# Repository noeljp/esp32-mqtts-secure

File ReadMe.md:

# 🛰️ Projet ESP32 MQTTs – Supervision de Machines Industrielles

Ce projet permet à un **ESP32** de se connecter à un **broker MQTT sécurisé (MQTTs)** afin de publier régulièrement des mesures issues d’une machine industrielle (armoire, four, frigo, etc.). Il inclut également la réception de commandes via MQTT.

---

## 🔧 Fonctionnalités principales

- Connexion sécurisée au Wi-Fi et au broker MQTT via TLS.
- Publication périodique de données au format JSON (via `ArduinoJson`).
- Abonnement à un topic pour recevoir des commandes.
- Adaptation dynamique selon le type de machine (armoire, four, frigo...).
- Intégration de capteurs analogiques (via `ADS1115`) et d'entrées numériques.
- Configuration centralisée dans `device_config.h` et `secrets.h`.

---

## 📁 Structure du projet

```bash
.
├── src/
│   ├── main.cpp            # Fichier principal Arduino (PlatformIO ou IDE Arduino)
│   ├── device_config.h     # Paramètres matériels de la machine (type, capteurs, I/O)
│   └── secrets.h           # Identifiants WiFi et certificats TLS (à créer manuellement)
├── include/
│   └── ...
├── certs/
│   ├── ca.crt              # Certificat racine du broker MQTT
│   └── ...
├── README.md               # Ce fichier
└── platformio.ini          # Configuration PlatformIO (si utilisé)
```

---

## 🔒 Fichier `secrets.h` (à créer)

Ce fichier contient les informations sensibles de connexion :

```cpp
#pragma once

const char* ssid = "VOTRE_SSID_WIFI";
const char* password = "VOTRE_MOT_DE_PASSE_WIFI";

const char* mqtt_server = "192.168.1.100";  // Adresse IP ou nom DNS du broker
const int mqtt_port = 8883;                // Port TLS

const char* mqtt_user = "utilisateur";
const char* mqtt_pass = "motdepasse";

// Certificat du broker (fichier .crt converti en chaîne C)
const char* ca_cert = R"EOF(
-----BEGIN CERTIFICATE-----
MIID...
...contenu du certificat...
-----END CERTIFICATE-----
)EOF";
```

---

## 🚀 Démarrage rapide

### 1. Pré-requis

- Carte **ESP32**
- Broker **Mosquitto** avec TLS et mot de passe (voir [guide d’installation ici](https://mosquitto.org/man/mosquitto.conf-5.html))
- Bibliothèques Arduino :
  - `PubSubClient`
  - `ArduinoJson`
  - `Adafruit_ADS1X15`
  - `WiFiClientSecure`

### 2. Compilation

Avec PlatformIO :
```bash
pio run
pio upload
```

Avec Arduino IDE :
- Sélectionner la carte "ESP32 Dev Module"
- Ajouter manuellement les bibliothèques
- Uploader le code

---

## 🔁 Boucle principale

- Toutes les `10 secondes` :
  - Lecture des capteurs (PT100, humidité, tension, etc.)
  - Construction d’un **JSON structuré**
  - Envoi sur le topic : `test/topic`

Exemple de JSON publié :
```json
{
  "device_id": "ARM1",
  "type": "armoire",
  "status": "OK",
  "firmware": "1.0.0",
  "uptime": "12345",
  "pt100_1": {
    "value": 23.5,
    "unit": "°C",
    "type": "temperature"
  },
  ...
}
```

---

## 📥 Commandes via MQTT

Le code s'abonne automatiquement au topic `test/cmd`. Les commandes reçues peuvent être affichées ou traitées selon le besoin (fonction `callback()` à enrichir).

---

## 🛠️ Configuration machine

Le fichier `device_config.h` permet d’adapter le programme à différents types de machines :

```cpp
const char* machine_type = "armoire"; // "four", "frigo", etc.
```

Chaque type dispose de :
- Ses capteurs spécifiques
- Sa logique d'initialisation (`initMachine`)
- Ses données personnalisées dans `fillMachineData`

---

## ✅ Extensions possibles

- Support de la reconnection automatique au WiFi
- Gestion de l’OTA (mise à jour firmware via réseau)
- Affichage sur écran OLED/TFT
- Ajout de watchdog

---

## 📬 Exemple de configuration côté Mosquitto

```conf
listener 8883
cafile /etc/mosquitto/certs/ca.crt
require_certificate false
allow_anonymous false
password_file /etc/mosquitto/passwd
```

---

## 📖 Auteurs et licence

Projet développé dans le cadre d’une supervision industrielle personnalisable par [Votre Nom / Équipe].

Licence : MIT (ou autre selon votre choix)

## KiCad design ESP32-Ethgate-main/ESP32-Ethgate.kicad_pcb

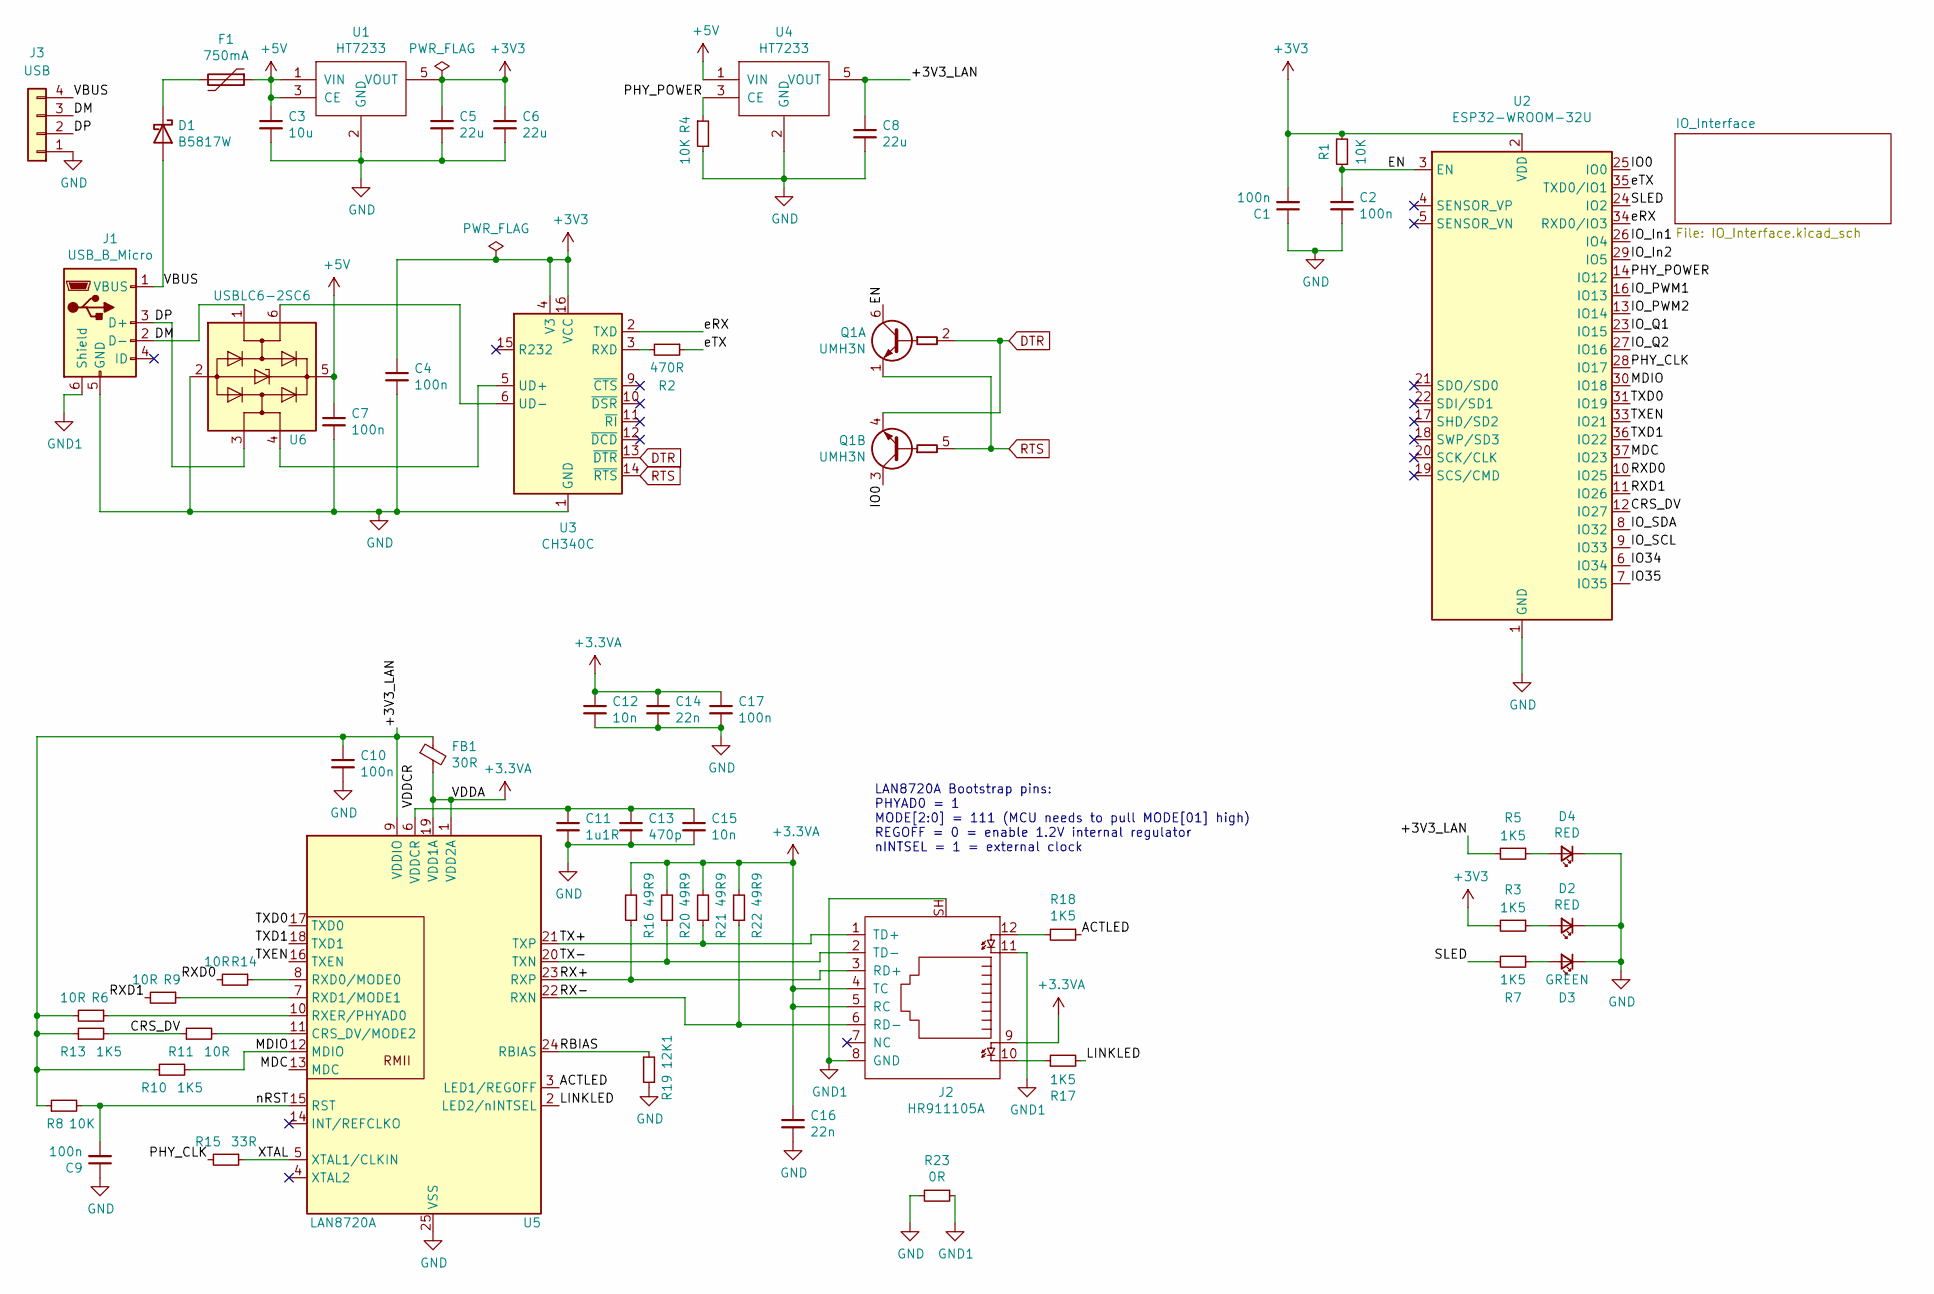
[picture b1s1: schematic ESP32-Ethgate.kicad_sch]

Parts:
C1, C2, C4, C7, C9, C10, C17: 100n; C_0603_1608Metric
C3: 10u; C_0805_2012Metric
C5, C6, C8: 22u; C_0805_2012Metric
C11: 1u1R; C_0603_1608Metric
C12, C15: 10n; C_0603_1608Metric
C13: 470p; C_0603_1608Metric
C14, C16: 22n; C_0603_1608Metric
D1: B5817W; D_SOD-323_HandSoldering
D2, D4: RED; LED_0603_1608Metric_Castellated
D3: GREEN; LED_0603_1608Metric_Castellated
F1: 750mA; Fuse_0805_2012Metric_Pad1.15x1.40mm_HandSolder
FB1: 30R; L_0603_1608Metric
J1: USB_B_Micro; USB_Micro-B_CNC_C10418
J2: HR911105A; RJ45_Hanrun_HR911105A_Oval
J3: USB; Molex_PicoBlade_53047-0410_1x04_P1.25mm_Vertical
Q1: UMH3N; SOT-363_SC-70-6_Handsoldering
R1, R4, R8: 10K; R_0603_1608Metric
R2: 470R; R_0603_1608Metric
R3, R5, R7, R10, R13, R17, R18: 1K5; R_0603_1608Metric
R6, R9, R11, R14: 10R; R_0603_1608Metric
R15: 33R; R_0603_1608Metric
R16, R20, R21, R22: 49R9; R_0603_1608Metric
R19: 12K1; R_0603_1608Metric
R23: 0R; R_0603_1608Metric
U1, U4: HT7233; SOT-23-5
U2: ESP32-WROOM-32U; ESP32-WROOM-32U-HandSoldering
U3: CH340C; SOIC-16_3.9x9.9mm_P1.27mm
U5: LAN8720A; QFN-24-1EP_4x4mm_P0.5mm_EP2.6x2.6mm
U6: USBLC6-2SC6; SOT-23-6_Handsoldering

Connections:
+3.3VA: C12.1, C14.1, C16.1, C17.1, FB1.2, J2.4 (TC), J2.5 (RC), J2.9, R16.2, R20.2, R21.2, R22.2, U5.1 (VDD2A), U5.19 (VDD1A)
+3V3: C1.2, C4.1, C5.1, C6.1, R1.2, R3.2, U1.5 (VOUT), U2.2 (VDD), U3.4 (V3), U3.16 (VCC); also elsewhere on the board
+5V: C3.1, C7.1, F1.1, U1.1 (VIN), U1.3 (CE), U4.1 (VIN), U6.5 (VBUS)
/+3V3_LAN: C8.1, C10.1, FB1.1, R5.2, R6.2, R8.1, R10.1, R13.1, U4.5 (VOUT), U5.9 (VDDIO)
/ACTLED: R18.1, U5.3 (LED1/REGOFF)
/CRS_DV: R11.1, R13.2, U2.12 (IO27)
/DM: J1.2 (D-), J3.3, U6.1 (I/O1)
/DP: J1.3 (D+), J3.2, U6.3 (I/O2)
/EN: C2.1, Q1.6 (C1), R1.1, U2.3 (EN)
/IO0: Q1.3 (C2), U2.25 (IO0)
/IO34: U2.6 (IO34)
/IO35: U2.7 (IO35)
/IO_In1: U2.26 (IO4); also elsewhere on the board
/IO_In2: U2.29 (IO5); also elsewhere on the board
/IO_PWM1: U2.16 (IO13); also elsewhere on the board
/IO_PWM2: U2.13 (IO14); also elsewhere on the board
/IO_Q1: U2.23 (IO15); also elsewhere on the board
/IO_Q2: U2.27 (IO16); also elsewhere on the board
/IO_SCL: U2.9 (IO33); also elsewhere on the board
/IO_SDA: U2.8 (IO32); also elsewhere on the board
/LINKLED: R17.2, U5.2 (LED2/nINTSEL)
/MDC: U2.37 (IO23), U5.13 (MDC)
/MDIO: R10.2, U2.30 (IO18), U5.12 (MDIO)
/PHY_CLK: R15.2, U2.28 (IO17)
/PHY_POWER: R4.1, U2.14 (IO12), U4.3 (CE)
/RBIAS: R19.2, U5.24 (RBIAS)
/RX+: J2.3 (RD+), R16.1, U5.23 (RXP)
/RX-: J2.6 (RD-), R22.1, U5.22 (RXN)
/RXD0: R14.2, U2.10 (IO25)
/RXD1: R9.2, U2.11 (IO26)
/SLED: R7.2, U2.24 (IO2)
/TX+: J2.1 (TD+), R21.1, U5.21 (TXP)
/TX-: J2.2 (TD-), R20.1, U5.20 (TXN)
/TXD0: U2.31 (IO19), U5.17 (TXD0)
/TXD1: U2.36 (IO22), U5.18 (TXD1)
/TXEN: U2.33 (IO21), U5.16 (TXEN)
/VBUS: D1.2 (A), J1.1 (VBUS), J3.4
/VDDCR: C11.1, C13.1, C15.1, U5.6 (VDDCR)
/XTAL: R15.1, U5.5 (XTAL1/CLKIN)
/eRX: U2.34 (RXD0/IO3), U3.2 (TXD)
/eTX: R2.1, U2.35 (TXD0/IO1)
/nRST: C9.2, R8.2, U5.15 (RST)
DTR: Q1.2 (B1), Q1.4 (E2), U3.13 (~DTR)
GND: C1.1, C2.2, C3.2, C4.2, C5.2, C6.2, C7.2, C8.2, C9.1, C10.2, C11.2, C12.2, C13.2, C14.2, C15.2, C16.2, C17.2, D2.1 (K), D3.1 (K), D4.1 (K), J1.5 (GND), J3.1, R4.2, R19.1, R23.2, U1.2 (GND), U2.1 (GND), U2.15 (GND), U2.38 (GND), U2.39 (GND), U3.1 (GND), U4.2 (GND), U5.25 (VSS), U6.2 (GND); also elsewhere on the board
GND1: J1.6 (Shield), J2.8 (GND), J2.11, J2.SH, R23.1
unnamed: D1.1 (K), F1.2
unnamed: D2.2 (A), R3.1
unnamed: D3.2 (A), R7.1
unnamed: D4.2 (A), R5.1
unnamed: J2.10, R17.1
unnamed: J2.12, R18.2
unnamed: R2.2, U3.3 (RXD)
unnamed: U3.5 (UD+), U6.4 (I/O2)
unnamed: U3.6 (UD-), U6.6 (I/O1)
unnamed: R11.2, U5.11 (CRS_DV/MODE2)
unnamed: R14.1, U5.8 (RXD0/MODE0)
unnamed: R9.1, U5.7 (RXD1/MODE1)
unnamed: R6.1, U5.10 (RXER/PHYAD0)
RTS: Q1.1 (E1), Q1.5 (B2), U3.14 (~RTS)

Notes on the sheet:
LAN8720A Bootstrap pins: PHYAD0 = 1 MODE[2:0] = 111 (MCU needs to pull MODE[01] high) REGOFF = 0 = enable 1.2V internal regulator nINTSEL = 1 = external clock

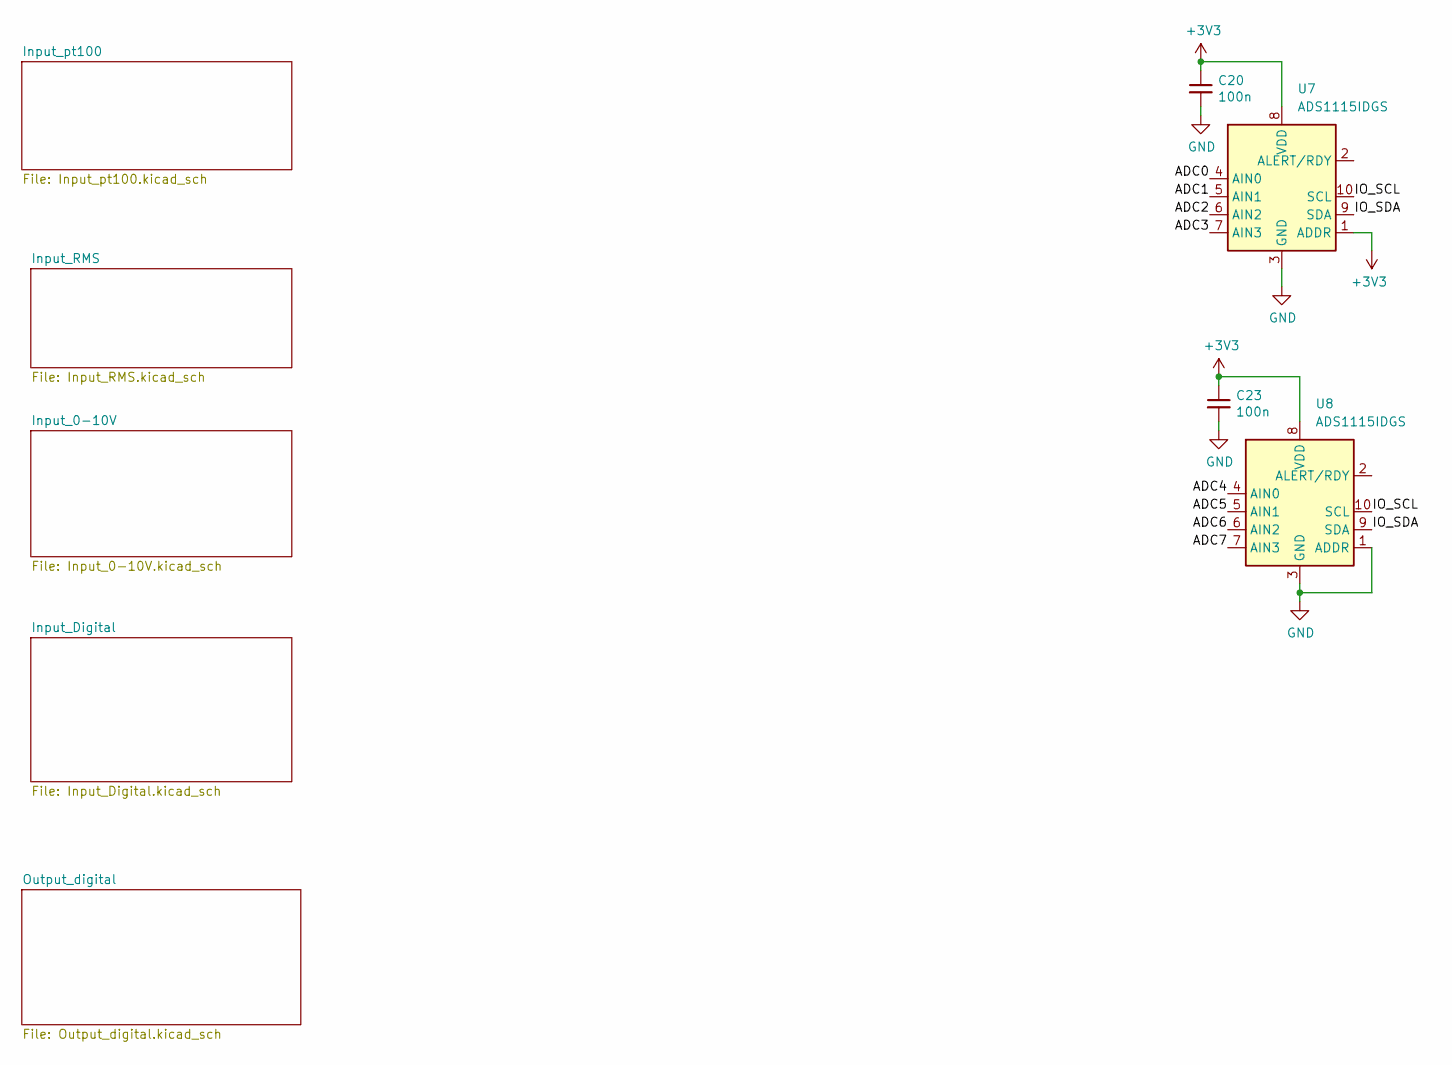
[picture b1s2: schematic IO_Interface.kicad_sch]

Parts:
C20, C23: 100n; C_0603_1608Metric
U7, U8: ADS1115IDGS; VSSOP-10_3x3mm_P0.5mm

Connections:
+3V3: C20.1, C23.1, U7.1 (ADDR), U7.8 (VDD), U8.8 (VDD); also elsewhere on the board
/IO_Interface/ADC0: U7.4 (AIN0)
/IO_Interface/ADC1: U7.5 (AIN1)
/IO_Interface/ADC2: U7.6 (AIN2)
/IO_Interface/ADC3: U7.7 (AIN3)
/IO_Interface/ADC4: U8.4 (AIN0)
/IO_Interface/ADC5: U8.5 (AIN1)
/IO_Interface/ADC6: U8.6 (AIN2)
/IO_Interface/ADC7: U8.7 (AIN3)
/IO_Interface/IO_SCL: U7.10 (SCL), U8.10 (SCL)
/IO_Interface/IO_SDA: U7.9 (SDA), U8.9 (SDA)
GND: C20.2, C23.2, U7.3 (GND), U8.1 (ADDR), U8.3 (GND); also elsewhere on the board

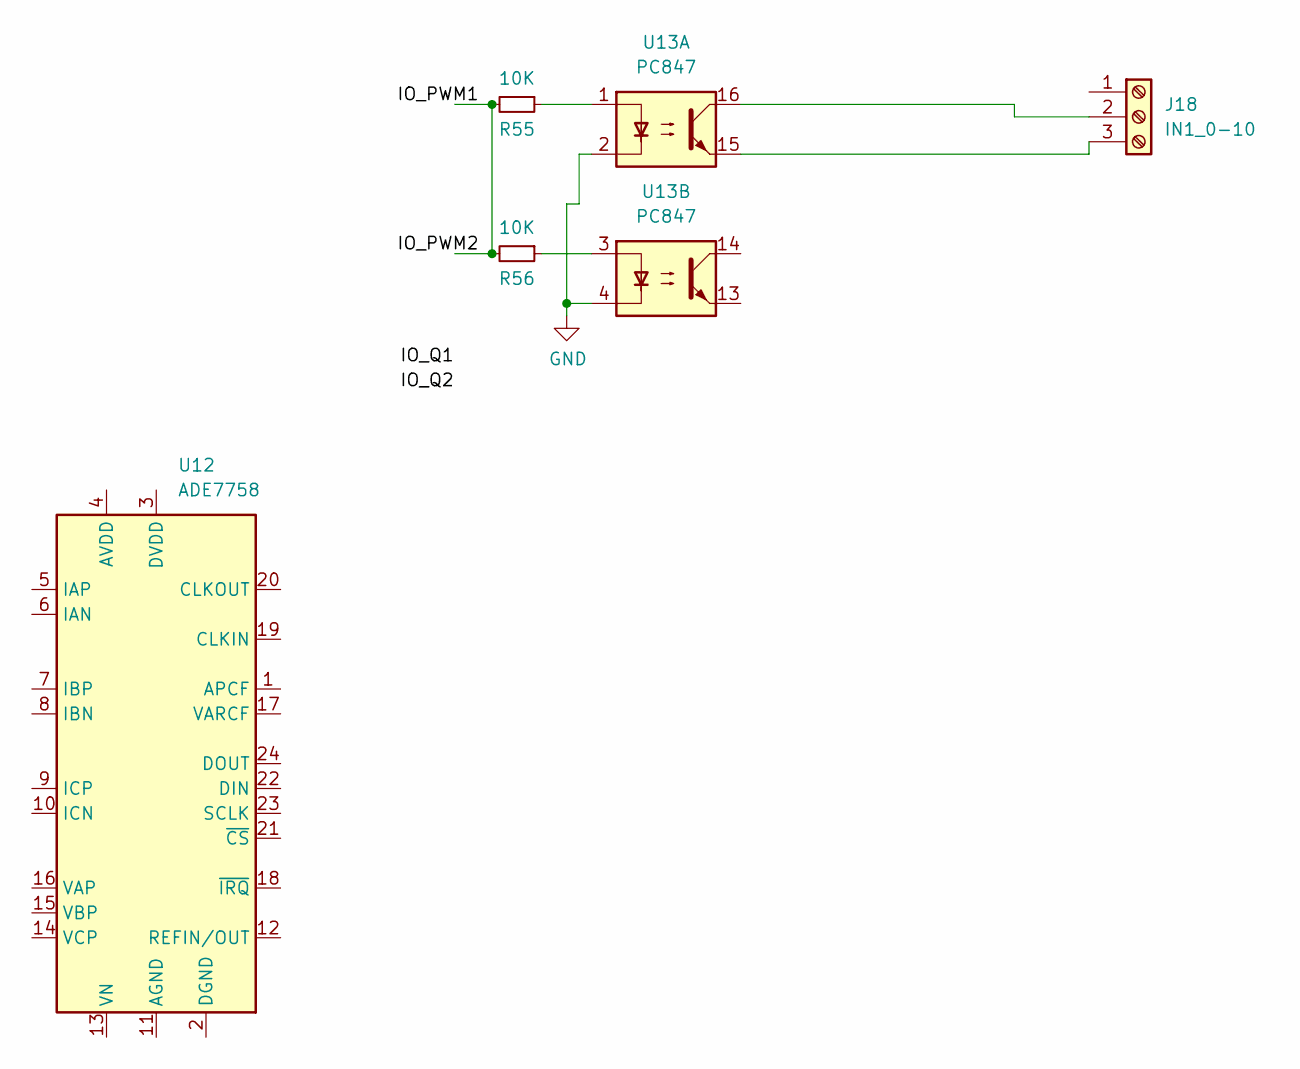
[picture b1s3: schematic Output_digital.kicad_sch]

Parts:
J18: IN1_0-10; PhoenixContact_SPT_2.5_3-H-5.0_1x03_P5.0mm_Horizontal
R55, R56: 10K; R_0603_1608Metric
U12: ADE7758; SOIC-24W_7.5x15.4mm_P1.27mm
U13: PC847; DIP-16_W7.62mm

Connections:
/IO_Interface/Output_digital/IO_PWM1: R55.2, R56.2
GND: U13.2, U13.4; also elsewhere on the board
unnamed: J18.2, U13.16
unnamed: J18.3, U13.15
unnamed: R55.1, U13.1
unnamed: R56.1, U13.3

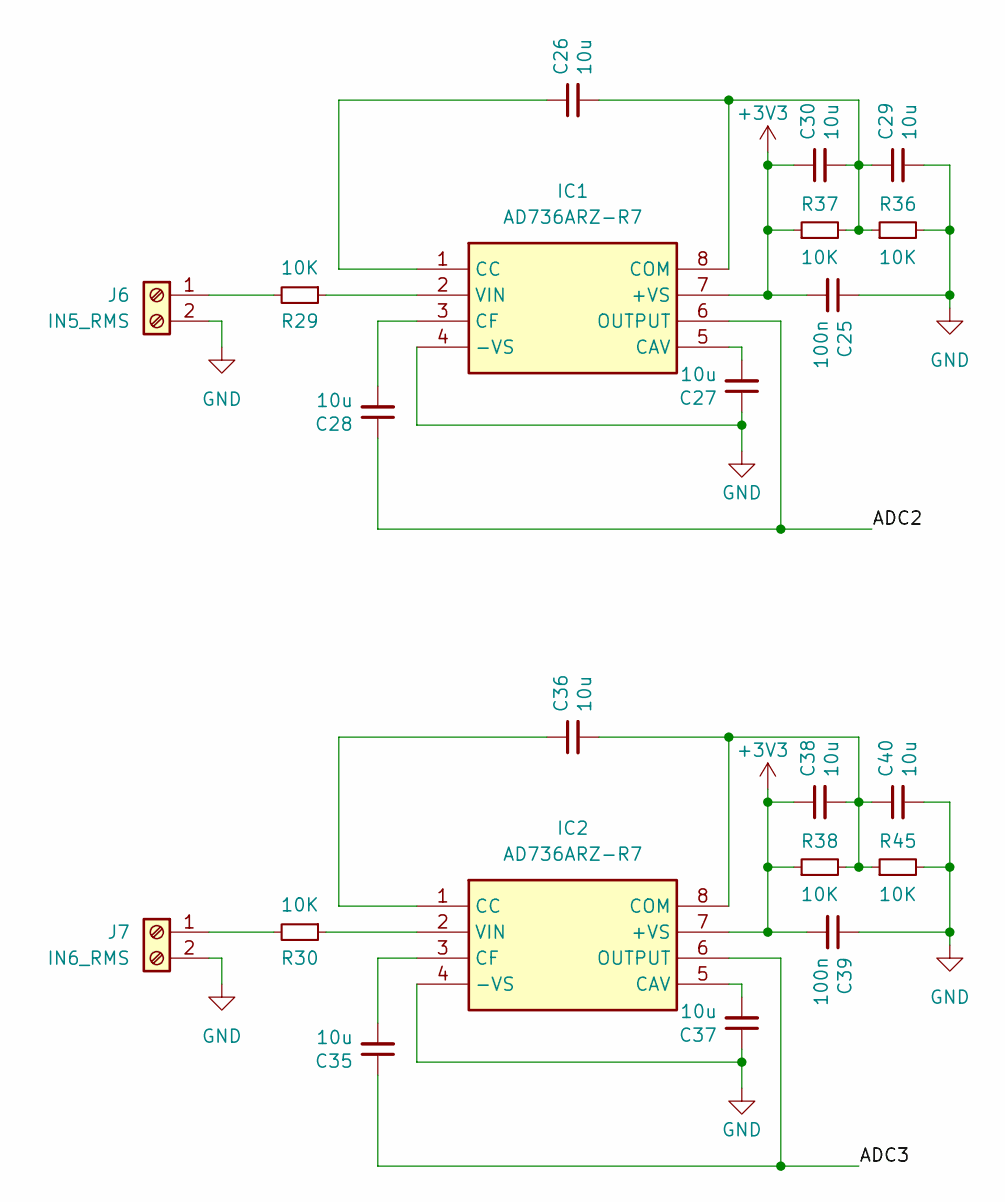
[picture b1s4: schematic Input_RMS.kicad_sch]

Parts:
C25, C39: 100n; C_0603_1608Metric
C26, C27, C28, C29, C30, C35, C36, C37, C38, C40: 10u; C_0805_2012Metric
IC1, IC2: AD736ARZ-R7; SOIC-8-1EP_3.9x4.9mm_P1.27mm_EP2.62x3.51mm; Mouser Part Number 584-AD736ARZ-R7
J6: IN5_RMS; PhoenixContact_SPT_2.5_2-H-5.0_1x02_P5.0mm_Horizontal
J7: IN6_RMS; PhoenixContact_SPT_2.5_2-H-5.0_1x02_P5.0mm_Horizontal
R29, R30, R36, R37, R38, R45: 10K; R_0603_1608Metric

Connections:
+3V3: C25.2, C30.1, C38.1, C39.2, IC1.7 (+VS), IC2.7 (+VS), R37.1, R38.1; also elsewhere on the board
/IO_Interface/Input_RMS/ADC2: C28.1, IC1.6 (OUTPUT)
/IO_Interface/Input_RMS/ADC3: C35.1, IC2.6 (OUTPUT)
GND: C25.1, C27.1, C29.2, C37.1, C39.1, C40.2, IC1.4 (-VS), IC2.4 (-VS), J6.2, J7.2, R36.2, R45.2; also elsewhere on the board
unnamed: C27.2, IC1.5 (CAV)
unnamed: C26.1, IC1.1 (CC)
unnamed: C28.2, IC1.3 (CF)
unnamed: C26.2, C29.1, C30.2, IC1.8 (COM), R36.1, R37.2
unnamed: IC1.2 (VIN), R29.1
unnamed: C37.2, IC2.5 (CAV)
unnamed: C36.1, IC2.1 (CC)
unnamed: C35.2, IC2.3 (CF)
unnamed: C36.2, C38.2, C40.1, IC2.8 (COM), R38.2, R45.1
unnamed: IC2.2 (VIN), R30.1
unnamed: J6.1, R29.2
unnamed: J7.1, R30.2

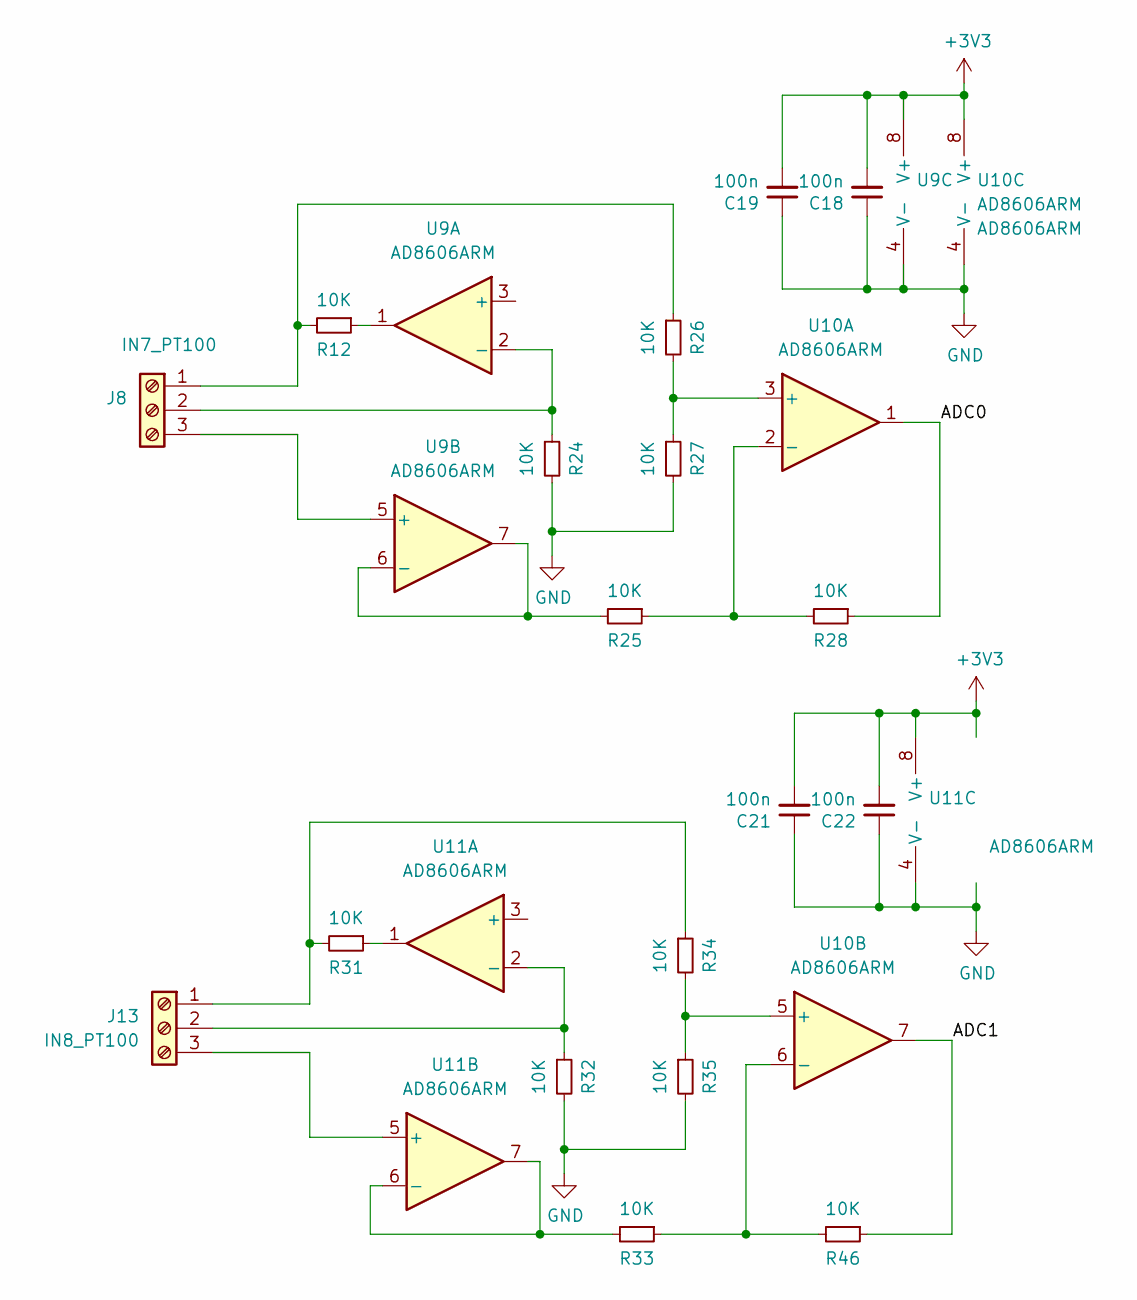
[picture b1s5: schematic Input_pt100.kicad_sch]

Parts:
C18, C19, C21, C22: 100n; C_0603_1608Metric
J8: IN7_PT100; PhoenixContact_SPT_2.5_3-H-5.0_1x03_P5.0mm_Horizontal
J13: IN8_PT100; PhoenixContact_SPT_2.5_3-H-5.0_1x03_P5.0mm_Horizontal
R12, R24, R25, R26, R27, R28, R31, R32, R33, R34, R35, R46: 10K; R_0603_1608Metric
U9, U10, U11: AD8606ARM; MSOP-8_3x3mm_P0.65mm

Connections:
+3V3: C18.2, C19.2, C21.2, C22.2, U9.8 (V+), U10.8 (V+), U11.8 (V+); also elsewhere on the board
/IO_Interface/Input_pt100/ADC0: R28.1, U10.1
/IO_Interface/Input_pt100/ADC1: R46.1, U10.7
GND: C18.1, C19.1, C21.1, C22.1, R24.2, R27.2, R32.2, R35.2, U9.4 (V-), U10.4 (V-), U11.4 (V-); also elsewhere on the board
unnamed: J8.1, R12.2, R26.1
unnamed: J8.2, R24.1, U9.2 (-)
unnamed: J8.3, U9.5 (+)
unnamed: J13.1, R31.2, R34.1
unnamed: J13.2, R32.1, U11.2 (-)
unnamed: J13.3, U11.5 (+)
unnamed: R12.1, U9.1
unnamed: R31.1, U11.1
unnamed: R25.2, U9.6 (-), U9.7
unnamed: R26.2, R27.1, U10.3 (+)
unnamed: R25.1, R28.2, U10.2 (-)
unnamed: R34.2, R35.1, U10.5 (+)
unnamed: R33.1, R46.2, U10.6 (-)
unnamed: R33.2, U11.6 (-), U11.7

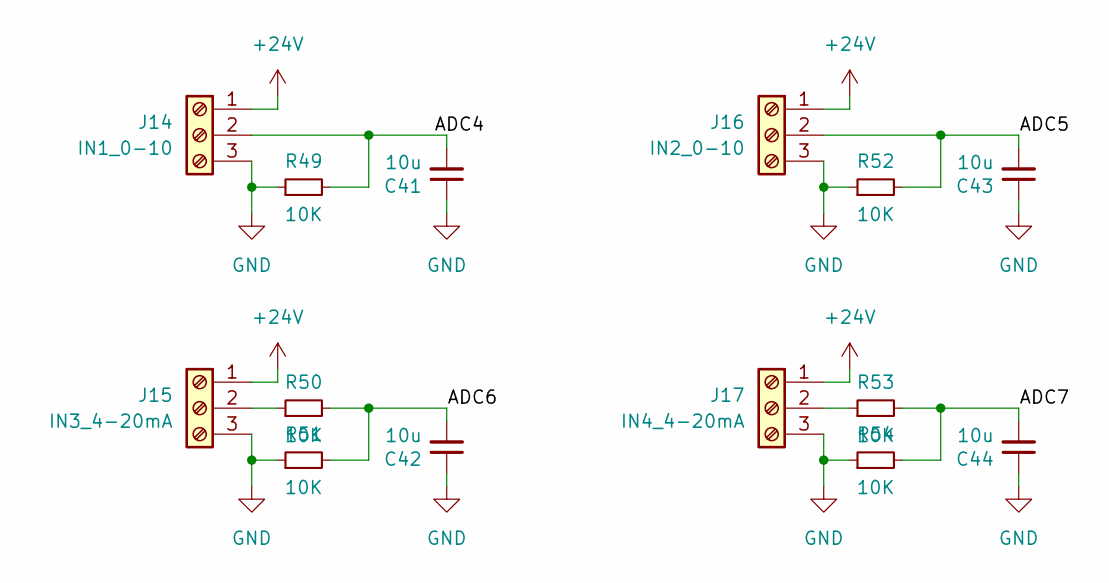
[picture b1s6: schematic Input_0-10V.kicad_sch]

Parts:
C41, C42, C43, C44: 10u; C_0805_2012Metric
J14: IN1_0-10; PhoenixContact_SPT_2.5_3-H-5.0_1x03_P5.0mm_Horizontal
J15: IN3_4-20mA; PhoenixContact_SPT_2.5_3-H-5.0_1x03_P5.0mm_Horizontal
J16: IN2_0-10; PhoenixContact_SPT_2.5_3-H-5.0_1x03_P5.0mm_Horizontal
J17: IN4_4-20mA; PhoenixContact_SPT_2.5_3-H-5.0_1x03_P5.0mm_Horizontal
R49, R50, R51, R52, R53, R54: 10K; R_0603_1608Metric

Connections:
+24V: J14.1, J15.1, J16.1, J17.1
/IO_Interface/Input_0-10V/ADC4: C41.2, J14.2, R49.2
/IO_Interface/Input_0-10V/ADC5: C43.2, J16.2, R52.2
/IO_Interface/Input_0-10V/ADC6: C42.2, R50.2, R51.2
/IO_Interface/Input_0-10V/ADC7: C44.2, R53.2, R54.2
GND: C41.1, C42.1, C43.1, C44.1, J14.3, J15.3, J16.3, J17.3, R49.1, R51.1, R52.1, R54.1; also elsewhere on the board
unnamed: J15.2, R50.1
unnamed: J17.2, R53.1

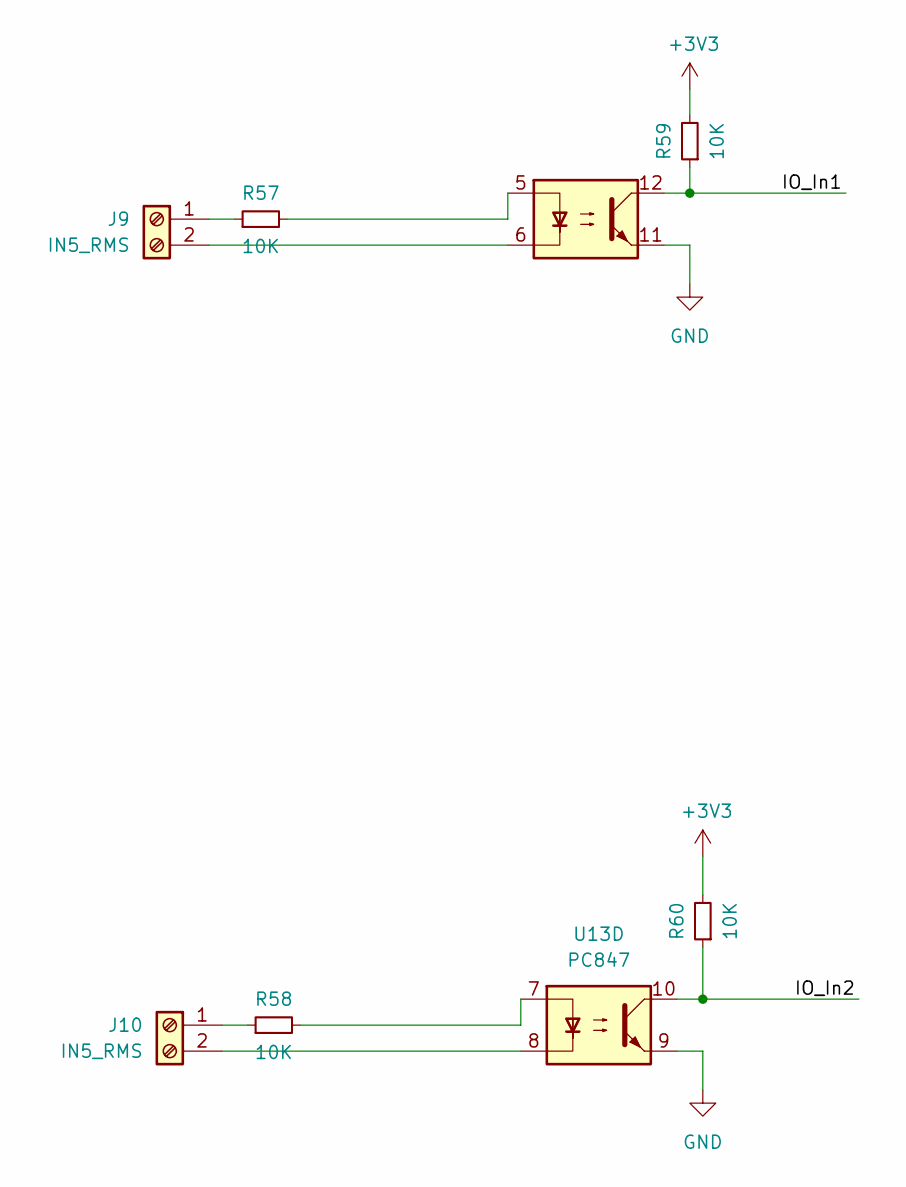
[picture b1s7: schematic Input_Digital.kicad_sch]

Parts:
J9, J10: IN5_RMS; PhoenixContact_SPT_2.5_2-H-5.0_1x02_P5.0mm_Horizontal
R57, R58, R59, R60: 10K; R_0603_1608Metric
U13: PC847; DIP-16_W7.62mm

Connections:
unnamed: J9.1, R57.1
unnamed: J9.2, U13.6
unnamed: J10.1, R58.1
unnamed: J10.2, U13.8
unnamed: R57.2, U13.5
unnamed: R58.2, U13.7
unnamed: R59.1, U13.12
unnamed: R59.2, R60.2
unnamed: R60.1, U13.10

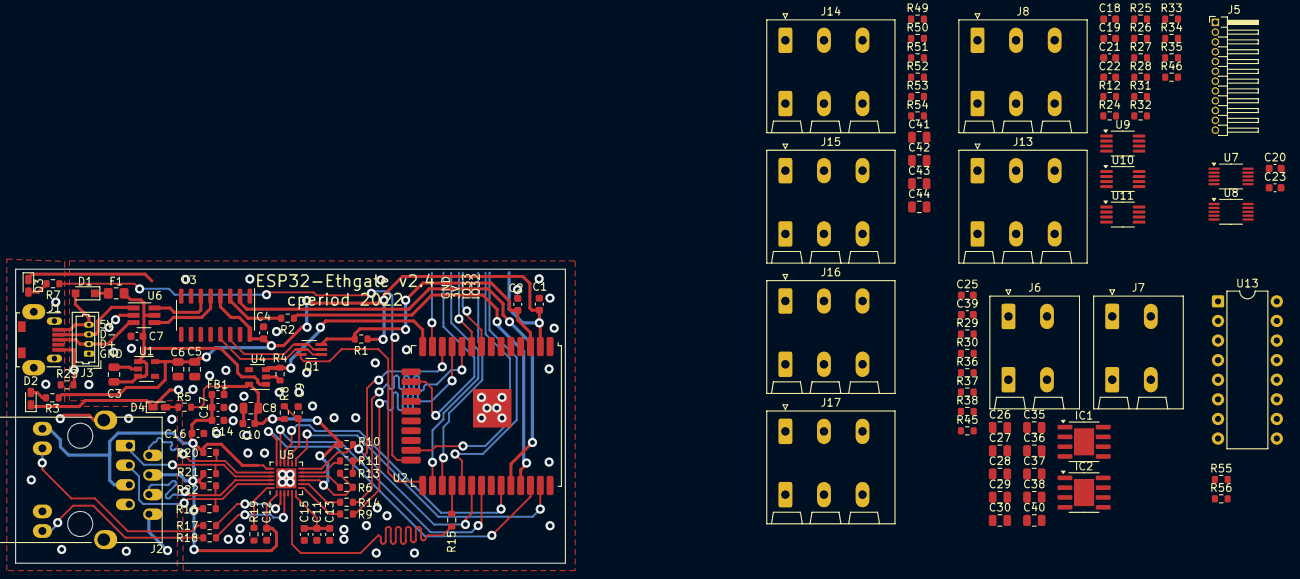
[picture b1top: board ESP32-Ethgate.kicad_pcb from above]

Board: 2 copper layers, 71.2 x 38.1 mm, 120 parts (0 on the bottom side), 99 nets.

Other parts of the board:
J5: Conn_01x12; PinHeader_1x12_P1.27mm_Horizontal

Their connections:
+3V3: J5.11; also elsewhere on the board
/IO_In1: J5.1; also elsewhere on the board
/IO_In2: J5.2; also elsewhere on the board
/IO_PWM1: J5.3; also elsewhere on the board
/IO_PWM2: J5.4; also elsewhere on the board
/IO_Q1: J5.5; also elsewhere on the board
/IO_Q2: J5.6; also elsewhere on the board
/IO_SCL: J5.8; also elsewhere on the board
/IO_SDA: J5.7; also elsewhere on the board
GND: J5.12; also elsewhere on the board

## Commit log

2025-04-13 Initial commit - projet MQTTs ESP32
2025-04-13 Mise à jour du main.cpp avec client MQTTs sécurisé
2025-04-13 Ajout de secrets_template.h et mise à jour du code + .gitignore
2025-04-13 Premier commit du projet ESP32 MQTTs
2025-04-14 Ajout des exécutables InfluxDBMQTT
2025-04-14 Ajout du Readme
2025-04-24 add ESP32KiCad File
